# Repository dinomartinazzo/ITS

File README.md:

# Project Specifications

### Project name :   ITS

    Date         :   Project started on 2023/02/01
    Author       :   Dino ^_^
    Description  :   Documents and Recipes
    Last Update  :   2026-11-26  16:41

### Contents:

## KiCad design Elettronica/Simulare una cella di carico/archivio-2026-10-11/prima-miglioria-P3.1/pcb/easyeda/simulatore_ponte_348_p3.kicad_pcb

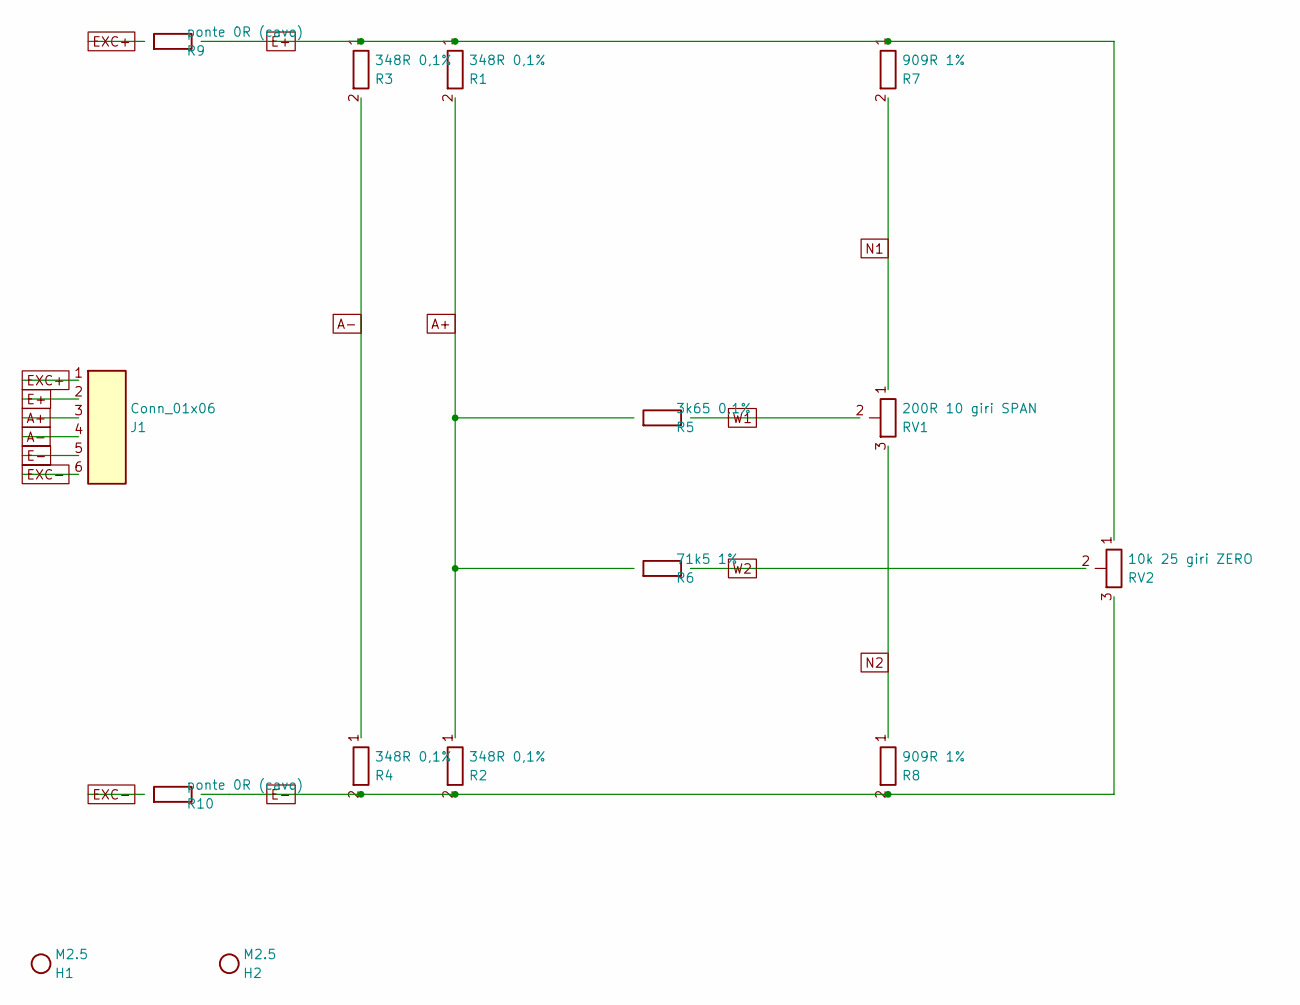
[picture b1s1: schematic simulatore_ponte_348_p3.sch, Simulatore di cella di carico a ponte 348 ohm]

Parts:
H1, H2: M2.5; MountingHole_2.7mm_M2.5
J1: Conn_01x06; PinHeader_1x06_P2.54mm_Vertical
R1, R2, R3, R4: 348R 0,1%; R_Axial_DIN0207_P10.16mm_Rot90
R5: 3k65 0,1%; R_Axial_DIN0207_P10.16mm_Horizontal
R6: 71k5 1%; R_Axial_DIN0207_P10.16mm_Horizontal
R7, R8: 909R 1%; R_Axial_DIN0207_P10.16mm_Rot90
R9, R10: ponte 0R (cavo); R_Axial_DIN0207_P5.08mm_Horizontal
RV1: 200R 10 giri SPAN; PinHeader_1x03_P2.54mm_Vertical
RV2: 10k 25 giri ZERO; PinHeader_1x03_P2.54mm_Vertical

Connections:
A+: J1.3, R1.2, R2.1, R5.2, R6.2
A-: J1.4, R3.2, R4.1
E+: J1.2, R1.1, R3.1, R7.1, R9.1, RV2.1
E-: J1.5, R2.2, R4.2, R8.2, R10.1, RV2.3
EXC+: J1.1, R9.2
EXC-: J1.6, R10.2
N1: R7.2, RV1.1
N2: R8.1, RV1.3
W1: R5.1, RV1.2
W2: R6.1, RV2.2

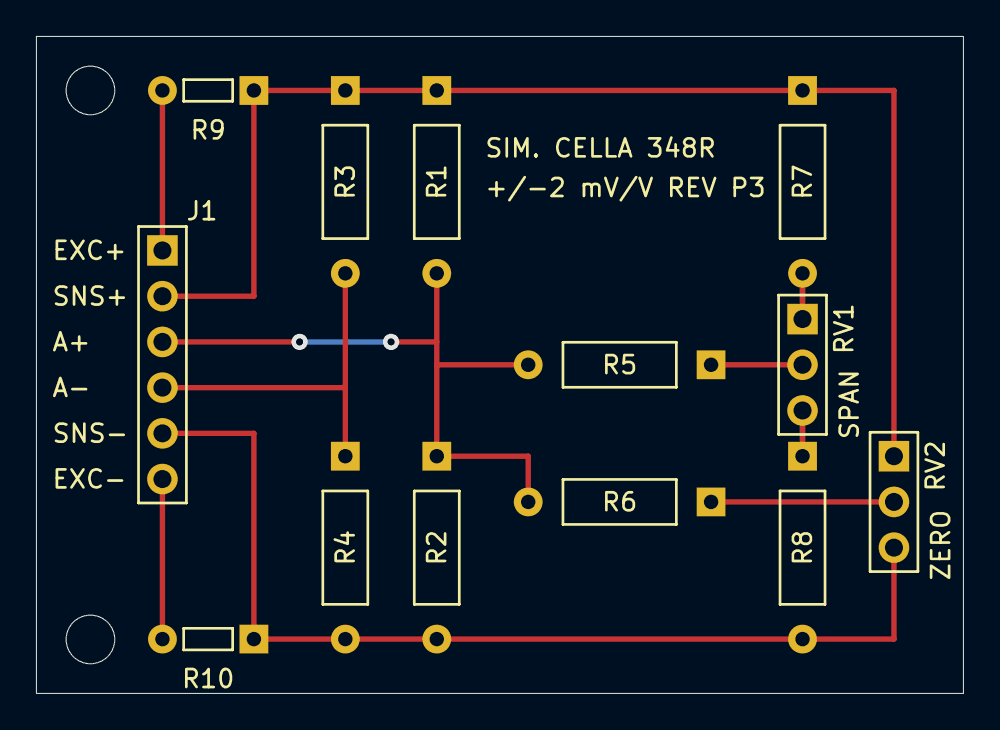
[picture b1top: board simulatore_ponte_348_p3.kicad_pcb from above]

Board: 2 copper layers, 51.5 x 36.5 mm, 15 parts (0 on the bottom side), 10 nets.

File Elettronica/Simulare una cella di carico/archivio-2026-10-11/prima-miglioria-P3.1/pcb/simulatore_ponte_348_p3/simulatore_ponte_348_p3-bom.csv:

"Rif","Q.ta","Valore","Footprint","Componente","Note"
"R1,R2,R3,R4","4","348R 0,1%","R_Axial_DIN0207_P10.16mm_Rot90","Strato metallico 1/4 W 0,1%, 25 ppm/°C","Stesso lotto, appaiate con il multimetro"
"R5","1","3k65 0,1%","R_Axial_DIN0207_P10.16mm_Horizontal","Strato metallico 1/4 W 0,1%","Determina il fondo scala"
"R6","1","71k5 1%","R_Axial_DIN0207_P10.16mm_Horizontal","Strato metallico 1/4 W 1%","Agisce solo sullo zero"
"R7,R8","2","909R 1%","R_Axial_DIN0207_P10.16mm_Rot90","Strato metallico 1/4 W 1% (0,1% se disponibili)","In serie al multigiri RV1"
"R9,R10","2","ponticello 0R","R_Axial_DIN0207_P5.08mm_Horizontal","Filo nudo o resistenza 0 ohm","Da montare sempre; sostituibili con 0,5-2 ohm per simulare il cavo"
"RV1","1","200R 10 giri","PinHeader_1x03_P2.54mm_Vertical","Multigiri 200 ohm, strato metallico (già disponibile)","Pin 1 = lato R7, 2 = cursore, 3 = lato R8; SPAN"
"RV2","1","10k 25 giri","PinHeader_1x03_P2.54mm_Vertical","Bourns 3296W-1-103LF","Pin 1 = E+, 2 = cursore, 3 = E-; ZERO. Impronta generica a 3 poli; verificare ingombro e orientamento prima del montaggio diretto, oppure collegare con tre fili."
"J1","1","Conn_01x06","PinHeader_1x06_P2.54mm_Vertical","Pin header 1x6 passo 2,54 mm","1 EXC+, 2 SENSE+, 3 A+, 4 A-, 5 SENSE-, 6 EXC-"
"H1,H2","2","M2.5","MountingHole_2.7mm_M2.5","Distanziale M2,5",""
